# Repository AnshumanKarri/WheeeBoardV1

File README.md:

# WheeeBoardV1

This README is a work in progress.

## Parts list: 
| Part | Part Name | Quanity |
|-----| ------ | ----- |
| Microcontroller | Nice!Nano V2 | 2 |
| Switches | Choc V1 | 36 |
| Diodes | Semtech 1N4148W SMD diodes | 36 |
| Battery Jack | JST PH 2.00mm battery jack | 2 |
| Power Switch | Alps miniature SPDT switch | 2 |
| Reset Button | Panasonic miniature momentary button | 2 |
| Rotary Encoder | ALPS EC12E2440301 | 2 |
| Rubber Feet |

## Tools list:

| Tool | Tool Name |
| ----- | ----- |
| Soldering Iron | Pine64 Pinecil |
| Solder Wire | Kester "44" 63/37 o.020" Solder Wire |
| Solder Flux | Kester 951 Soldering Flux |
| Solder Sucker |  |
| Solder tip cleaner |  |
| 3D printer | Bambu Lab A1 Mini |

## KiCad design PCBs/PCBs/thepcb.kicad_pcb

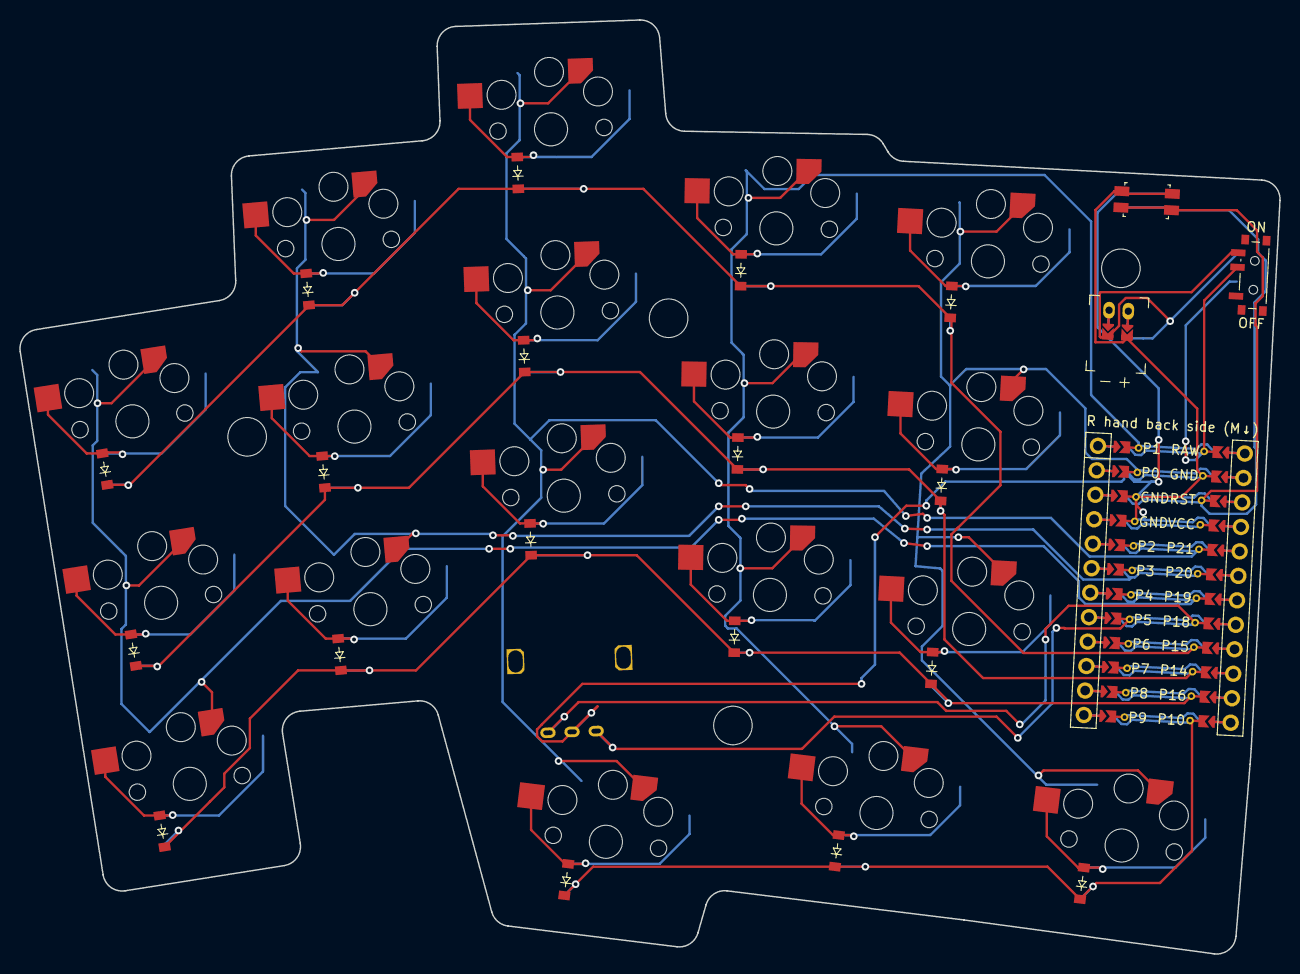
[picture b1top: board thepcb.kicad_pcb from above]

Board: 2 copper layers, 130.6 x 96.8 mm, 41 parts (1 on the bottom side), 35 nets.

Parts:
D1, D2, D3, D4, D5, D6, D7, D8, D9, D10, D11, D12, D13, D14, D15, D16, D17, D18: diode_tht_sod123
JST1: battery_connector_jst_ph_2
MCU1: mcu_nice_nano
PWR1: power_switch_smd_side
RE1: rotary_encoder_ec11_ec12
RST1: reset_switch_smd_side
S1, S2, S3, S4, S5, S6, S7, S8, S9, S10, S11, S12, S13, S14, S15, S16, S17, S18: PG1350

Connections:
1_top: D16.2, S16.2
2_top: D17.2, S17.2
3_top: D18.2, S18.2
BAT_P: JST1.1, PWR1.1, PWR1.3
GND: JST1.2, MCU1.102, MCU1.121, MCU1.122, RE1.B, RST1.1, RST1.3
JST1_1: JST1.11, JST1.21, JST1.31
JST1_2: JST1.12, JST1.22, JST1.32
P0: MCU1.123, S13.1, S14.1, S15.1, S18.1
P1: MCU1.124, S10.1, S11.1, S12.1, S17.1
P5: MCU1.117, RE1.A
P10: D16.1, D17.1, D18.1, MCU1.112
P14: D2.1, D5.1, D8.1, D11.1, D14.1, MCU1.110
P15: D3.1, D6.1, D9.1, D12.1, D15.1, MCU1.109
P16: D1.1, D4.1, D7.1, D10.1, D13.1, MCU1.111
P18: MCU1.108, RE1.C
P19: MCU1.107, S1.1, S2.1, S3.1
P20: MCU1.106, S4.1, S5.1, S6.1
P21: MCU1.105, S7.1, S8.1, S9.1, S16.1
RAW: MCU1.101, PWR1.2
RST: MCU1.103, RST1.2, RST1.4
far_bottom: D13.2, S13.2
far_home: D14.2, S14.2
far_top: D15.2, S15.2
index_bottom: D10.2, S10.2
index_home: D11.2, S11.2
index_top: D12.2, S12.2
middle_bottom: D7.2, S7.2
middle_home: D8.2, S8.2
middle_top: D9.2, S9.2
pinkie_bottom: D1.2, S1.2
pinkie_home: D2.2, S2.2
pinkie_top: D3.2, S3.2
ring_bottom: D4.2, S4.2
ring_home: D5.2, S5.2
ring_top: D6.2, S6.2

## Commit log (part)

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2025-09-18 PCB files and case files
2025-09-18 KeyboardImages
